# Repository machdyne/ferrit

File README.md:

# FERRIT Digital Archival Platform

FERRIT is a century-scale digital archival platform based on Ferroelectric RAM.

This repo contains PCB layouts, schematics, firmware and documentation.

Find more information on the [FERRIT project page](https://machdyne.com/ferrit/).

## Hardware

FERRIT is a modular upgradable system with 3 component types:

- A controller
- A backplane
- Removable ferroelectric memory cards

The controller communicates with the memory cards over a SPI/QSPI bus and exposes the memory to an interface, such as a USB mass storage device.

### Specifications

- Max capacity: 256MB+
- Max addressable memory devices per memory card: 16
- Max addressable memory devices per system: 256
- Interface: Depends on controller
- Speed: Depend on controller

*Note: The max capacity assumes double-sided memory cards with 1MB ICs. Higher capacities may be possible in the future.*

### Components

| Board | Type | Notes |
| ----- | ---- | ----- |
| [FERRIT-CY](https://machdyne.com/product/ferrit-cy/) | Controller | RP2040 / USB-FS |
| [FERRIT-M8](https://machdyne.com/product/ferrit-m8-8mb/) | Memory card | 8 x SOP-16 |
| [FERRIT-1](https://machdyne.com/product/ferrit-1/) | Backplane + Controller | RP2040 / USB-FS / 1 memory card slot |
| [FERRIT-8](https://machdyne.com/product/ferrit-8/) | Backplane | 8 memory card slots (1U rack-mount) |
| [FERRIT-16](https://machdyne.com/product/ferrit-16/) | Backplane | 16 memory card slots |

## Firmware

The firmware can be updated by holding down the BOOT button while plugging in the USB cable, and then dragging and dropping a new UF2 file to the device.

You can build the firmware from source, if you have [pico-sdk](https://github.com/raspberrypi/pico-sdk) installed:

```
$ cd firmware/ferrit
$ mkdir build
$ cd build
$ cmake .. -DPICO_DEFAULT_BOOT_STAGE2_FILE=$PICO_SDK_PATH/src/rp2040/boot_stage2/boot2_generic_03h.S
$ make
```

## Pinouts

### Connector

The FERRIT controller and memory cards use the same form-factor and share certain signals:

| Pin | Controller | Memory Card |
| --- | ---------- | ----------- |
| 1 | QSPI\_SCLK | QSPI\_SCLK |
| 3 | GND | GND |
| 5 | QSPI\_SD0 | QSPI\_SD0 |
| 7 | GND | GND |
| 9 | QSPI\_SD1 | QSPI\_SD1 |
| 11 | GND | GND |
| 13 | QSPI\_SD2 | QSPI\_SD2 |
| 15 | GND | GND |
| 17 | QSPI\_SD3 | QSPI\_SD3 |
| 19 | GND | GND |
| 2 | QSPI\_SS | QSPI\_SS |
| 4 | SS0 | GND |
| 6 | CS0 | CS0 |
| 8 | CS1 | CS1 |
| 10 | CS2 | CS2 |
| 12 | CS3 | CS3 |
| 14 | SS1 | GND |
| 16 | SS2 | GND |
| 18 | SS3 | GND |
| 20 | PWR3V3 | PWR3V3 |

The slot select (SSx) signals determine which slot is selected, while the chip select (CSx) signals select an IC on that slot.

## License

The contents of this repo are released under the [Lone Dynamics Open License](LICENSE.md).

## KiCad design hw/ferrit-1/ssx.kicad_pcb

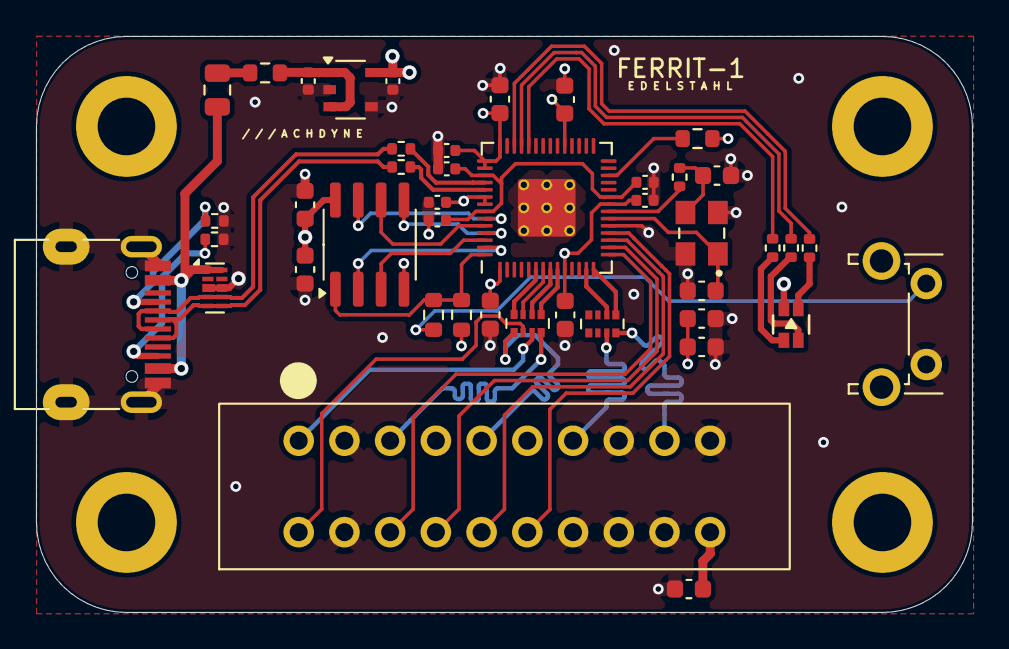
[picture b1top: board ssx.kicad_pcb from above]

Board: 4 copper layers, 52.0 x 32.0 mm, 47 parts (0 on the bottom side), 45 nets.

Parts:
C1, C2: 15pF; C_0603_1608Metric
C3, C10, C16, C17: 1uF; C_0402_1005Metric
C4, C6, C8, C9: 100nF; C_0402_1005Metric
C5, C7, C11, C12, C13, C15: 100nF; C_0603_1608Metric
C14: 1uF; C_0603_1608Metric
C19, C20: 22uF; C_0603_1608Metric
D1: LED_RGB_ANODE; LED_RGB_0606_CHANZON
F1: Fuse_Small; Fuse_0805_2012Metric
FB1: Ferrite_Bead_Small; R_0603_1608Metric
H1, H2, H3, H4: MountingHole; MountingHole_3.2mm_M3_DIN965_Pad
J1: USB_C_Receptacle_USB2.0_16P; USB_C_Receptacle_HRO_TYPE-C-31-M-12-BIG-PADS-PASTE
J2: Conn_02x10_Odd_Even; MACHDYNE_EDGE_SOCKET_20P
R1, R7: 10K; R_0603_1608Metric
R2, R3: 27R; R_0402_1005Metric
R4, R11, R12, R13: 1K; R_0402_1005Metric
R5, R6: 5K1; R_0402_1005Metric
R8: 1K; R_0603_1608Metric
RN1, RN2: 33R; R_Array_Convex_4x0402
SW1: BOOT; SW_Tactile_SPST_Angled_PTS645Vx39-2LFS
U1: RP2040; RP2040-QFN-56-OFFICIAL
U2: TPD4E05U06DQAR; Diodes_UDFN-10_1.0x2.5mm_P0.5mm
U3: M95P32-IXMNT/E; SOIC-8_3.9x4.9mm_P1.27mm
U4: NCP115; TSOP-5_1.65x3.05mm_P0.95mm
Y1: ECS-80-12-33-JGN-TR-12MHZ; XTAL_ECS-240-8-33-AGN-TR

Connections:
/BOOT: R8.1, SW1.1
/CS0: J2.6, U1.15 (GPIO12)
/CS1: J2.8, U1.16 (GPIO13)
/CS2: J2.10, U1.17 (GPIO14)
/CS3: J2.12, U1.18 (GPIO15)
/KQSPI_SCLK: J2.1, RN1.7 (R2.2)
/KQSPI_SD0: J2.5, RN1.8 (R1.2)
/KQSPI_SD1: J2.9, RN1.5 (R4.2)
/KQSPI_SD2: J2.13, RN2.7 (R2.2)
/KQSPI_SD3: J2.17, RN2.8 (R1.2)
/KSS: J2.2, RN1.6 (R3.2)
/LEDB: R13.2, U1.40 (GPIO28/ADC2)
/LEDG: R12.2, U1.39 (GPIO27/ADC1)
/LEDR: R11.2, U1.38 (GPIO26/ADC0)
/PWR1V1: C6.1, C8.1, C10.1, U1.23 (DVDD), U1.45 (VREG_VOUT), U1.50 (DVDD)
/PWR3V3: C3.1, C4.1, C5.1, C7.1, C9.1, C11.1, C12.1, C13.1, C14.1, C15.1, C17.1, C19.1, C20.1, D1.1 (A), J2.20, R1.1, R7.1, U1.1 (IOVDD), U1.10 (IOVDD), U1.22 (IOVDD), U1.33 (IOVDD), U1.42 (IOVDD), U1.43 (ADC_AVDD), U1.44 (VREG_VIN), U1.48 (USB_VDD), U1.49 (IOVDD), U3.8 (VCC), U4.5 (OUT)
/PWR5V0: C16.1, FB1.1, U4.1 (IN), U4.3 (EN)
/QSPI_IO0: RN1.1 (R1.1), U1.9 (GPIO7)
/QSPI_IO1: RN1.4 (R4.1), U1.6 (GPIO4)
/QSPI_IO2: RN2.2 (R2.1), U1.13 (GPIO10)
/QSPI_IO3: RN2.1 (R1.1), U1.14 (GPIO11)
/QSPI_SCLK: RN1.2 (R2.1), U1.8 (GPIO6)
/RP_QSPI_IO0: U1.53 (QSPI_SD0), U3.5 (DI(IO0))
/RP_QSPI_IO1: U1.55 (QSPI_SD1), U3.2 (DO(IO1))
/RP_QSPI_IO2: U1.54 (QSPI_SD2), U3.3 (IO2)
/RP_QSPI_IO3: U1.51 (QSPI_SD3), U3.7 (IO3)
/RP_QSPI_SCK: U1.52 (QSPI_SCLK), U3.6 (CLK)
/RP_QSPI_SS: R7.2, R8.2, U1.56 (QSPI_CSN), U3.1 (~CS)
/RUN: R1.2, U1.26 (RUN)
/SS: RN1.3 (R3.1), U1.7 (GPIO5)
/USBCDN: J1.A7 (D-), J1.B7 (D-), R3.1, U2.4, U2.7
/USBCDP: J1.A6 (D+), J1.B6 (D+), R2.1, U2.5, U2.6
/USBC_CC1: J1.A5 (CC1), R5.2
/USBC_CC2: J1.B5 (CC2), R6.2
/USBDN: R3.2, U1.46 (USB_DM)
/USBDP: R2.2, U1.47 (USB_DP)
/VBUS: F1.1, J1.A4 (VBUS), J1.A9 (VBUS), J1.B4 (VBUS), J1.B9 (VBUS), U2.1, U2.10
/XIN: C1.2, U1.20 (XIN), Y1.1 (IN/OUT)
/XOUT: R4.2, U1.21 (XOUT)
GND: C1.1, C2.2, C3.2, C4.2, C5.2, C6.2, C7.2, C8.2, C9.2, C10.2, C11.2, C12.2, C13.2, C14.2, C15.2, C16.2, C17.2, C19.2, C20.2, J1.A1 (GND), J1.A12 (GND), J1.B1 (GND), J1.B12 (GND), J1.S1 (SHIELD), J2.3, J2.4, J2.7, J2.11, J2.14, J2.15, J2.16, J2.18, J2.19, R5.1, R6.1, SW1.2, U1.19 (TESTEN), U1.57 (GND), U2.3 (VSS), U2.8 (VSS), U3.4 (GND), U4.2 (GND), U4.4 (GND2), Y1.2 (GND), Y1.4 (GND)
unnamed: D1.2 (BK), R13.1
unnamed: D1.4 (GK), R12.1
unnamed: D1.3 (RK), R11.1
unnamed: F1.2, FB1.2
unnamed: C2.1, R4.1, Y1.3 (OUT/IN)

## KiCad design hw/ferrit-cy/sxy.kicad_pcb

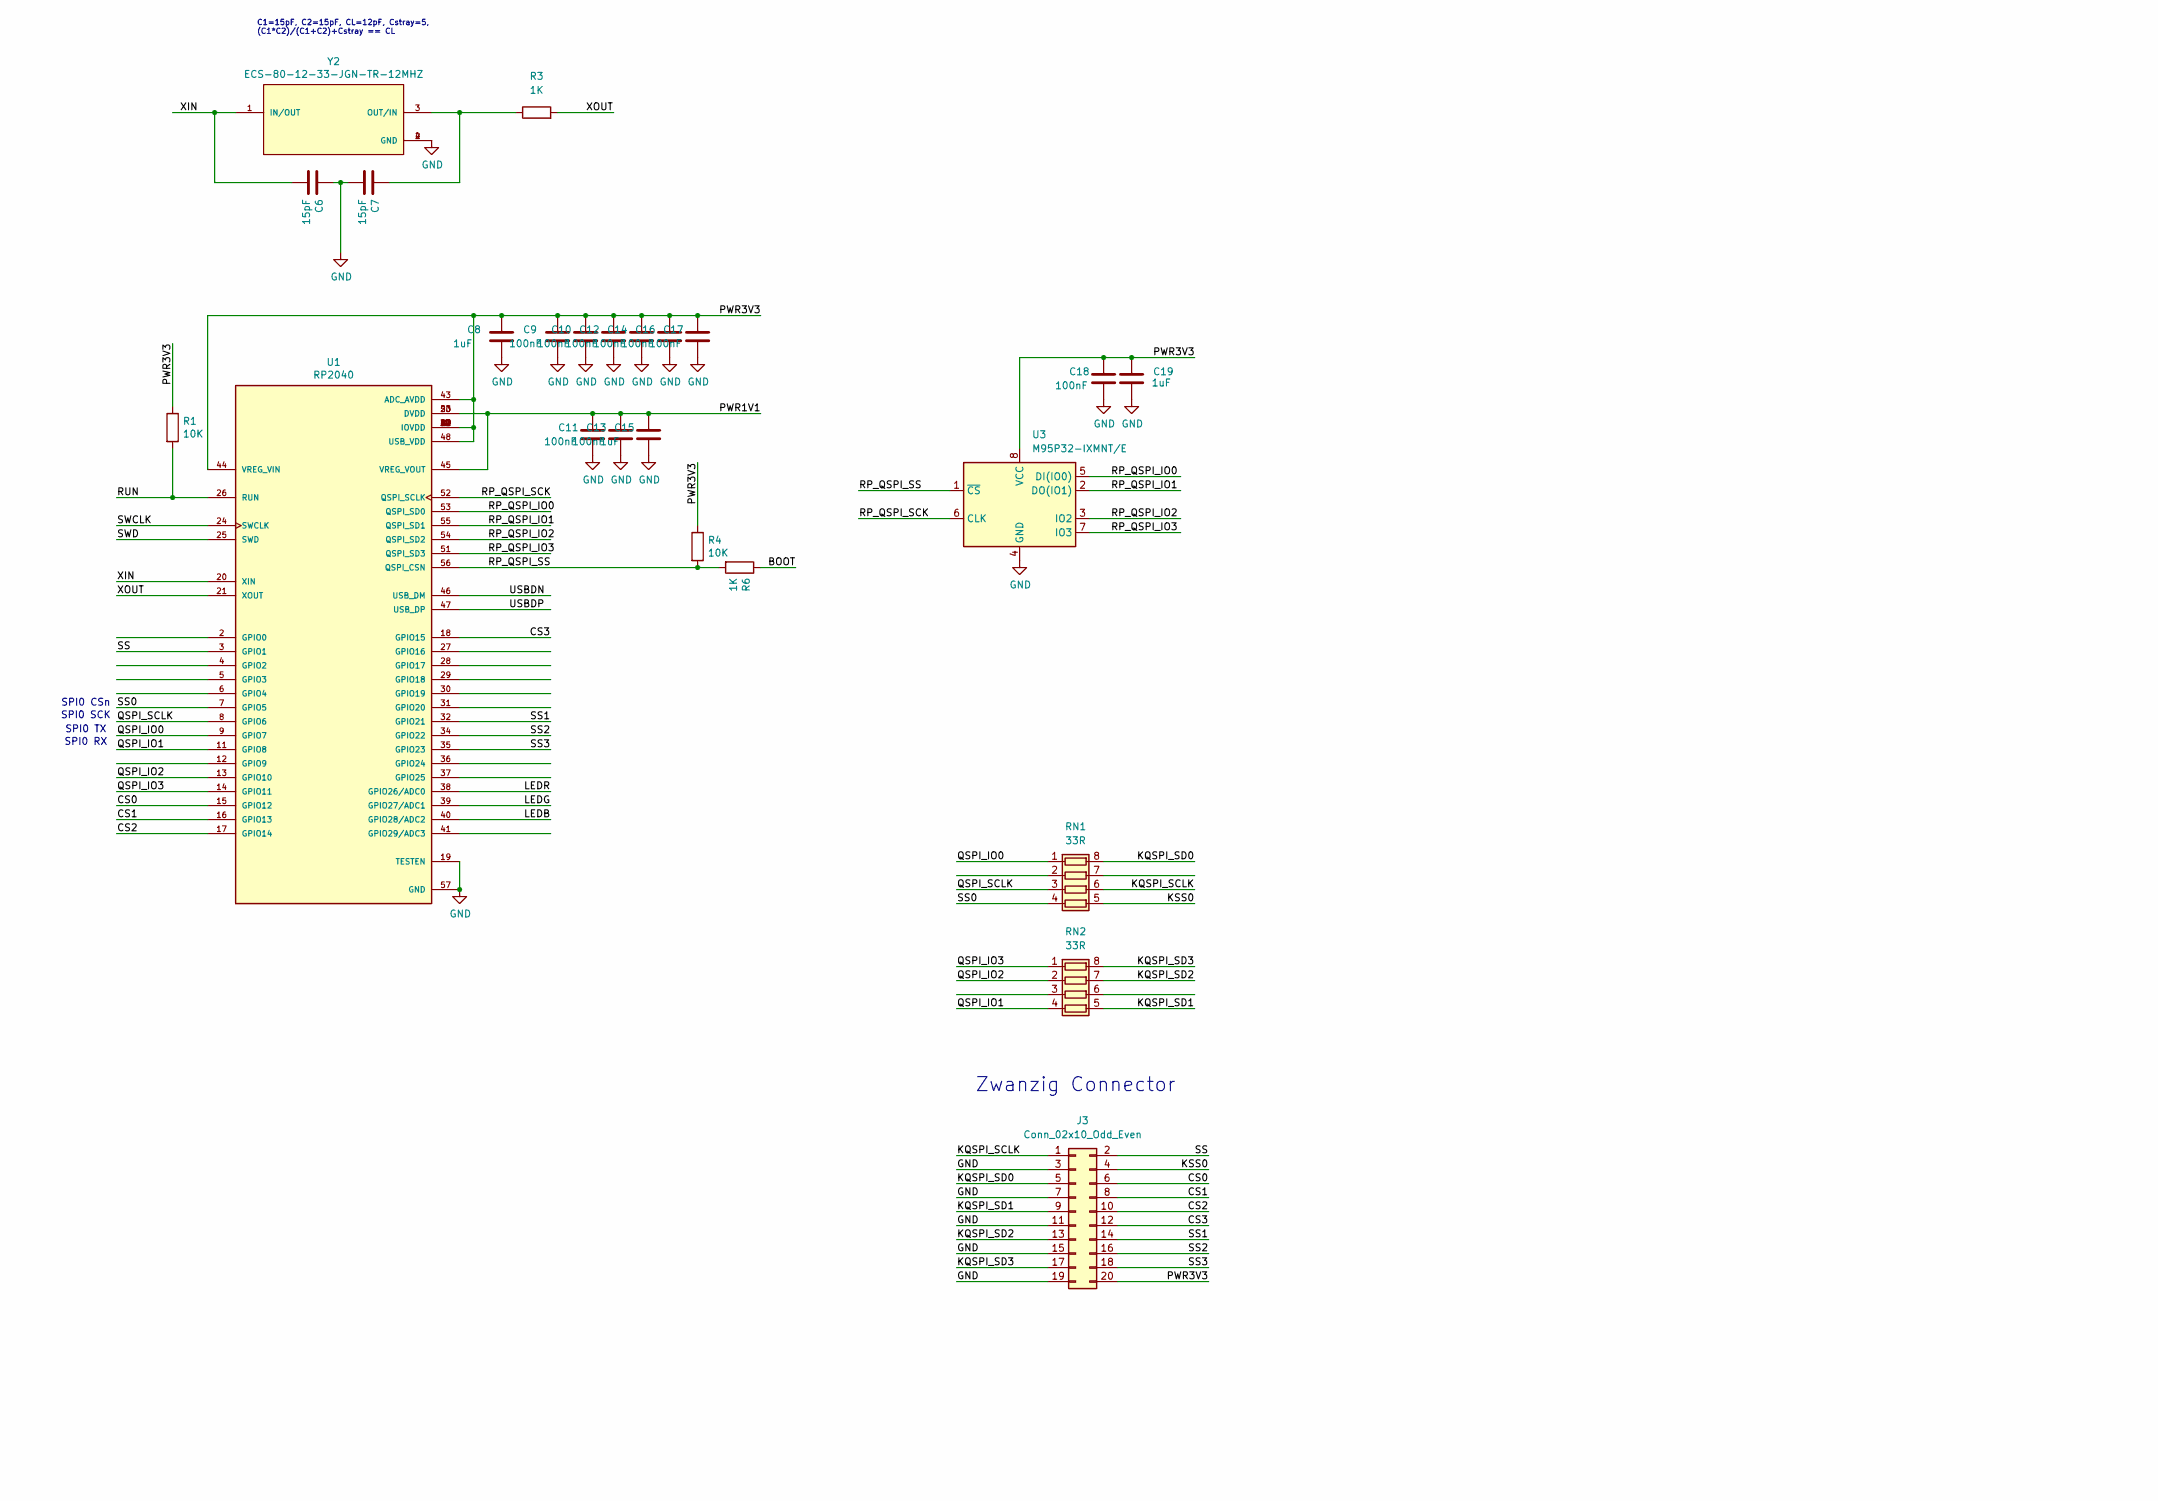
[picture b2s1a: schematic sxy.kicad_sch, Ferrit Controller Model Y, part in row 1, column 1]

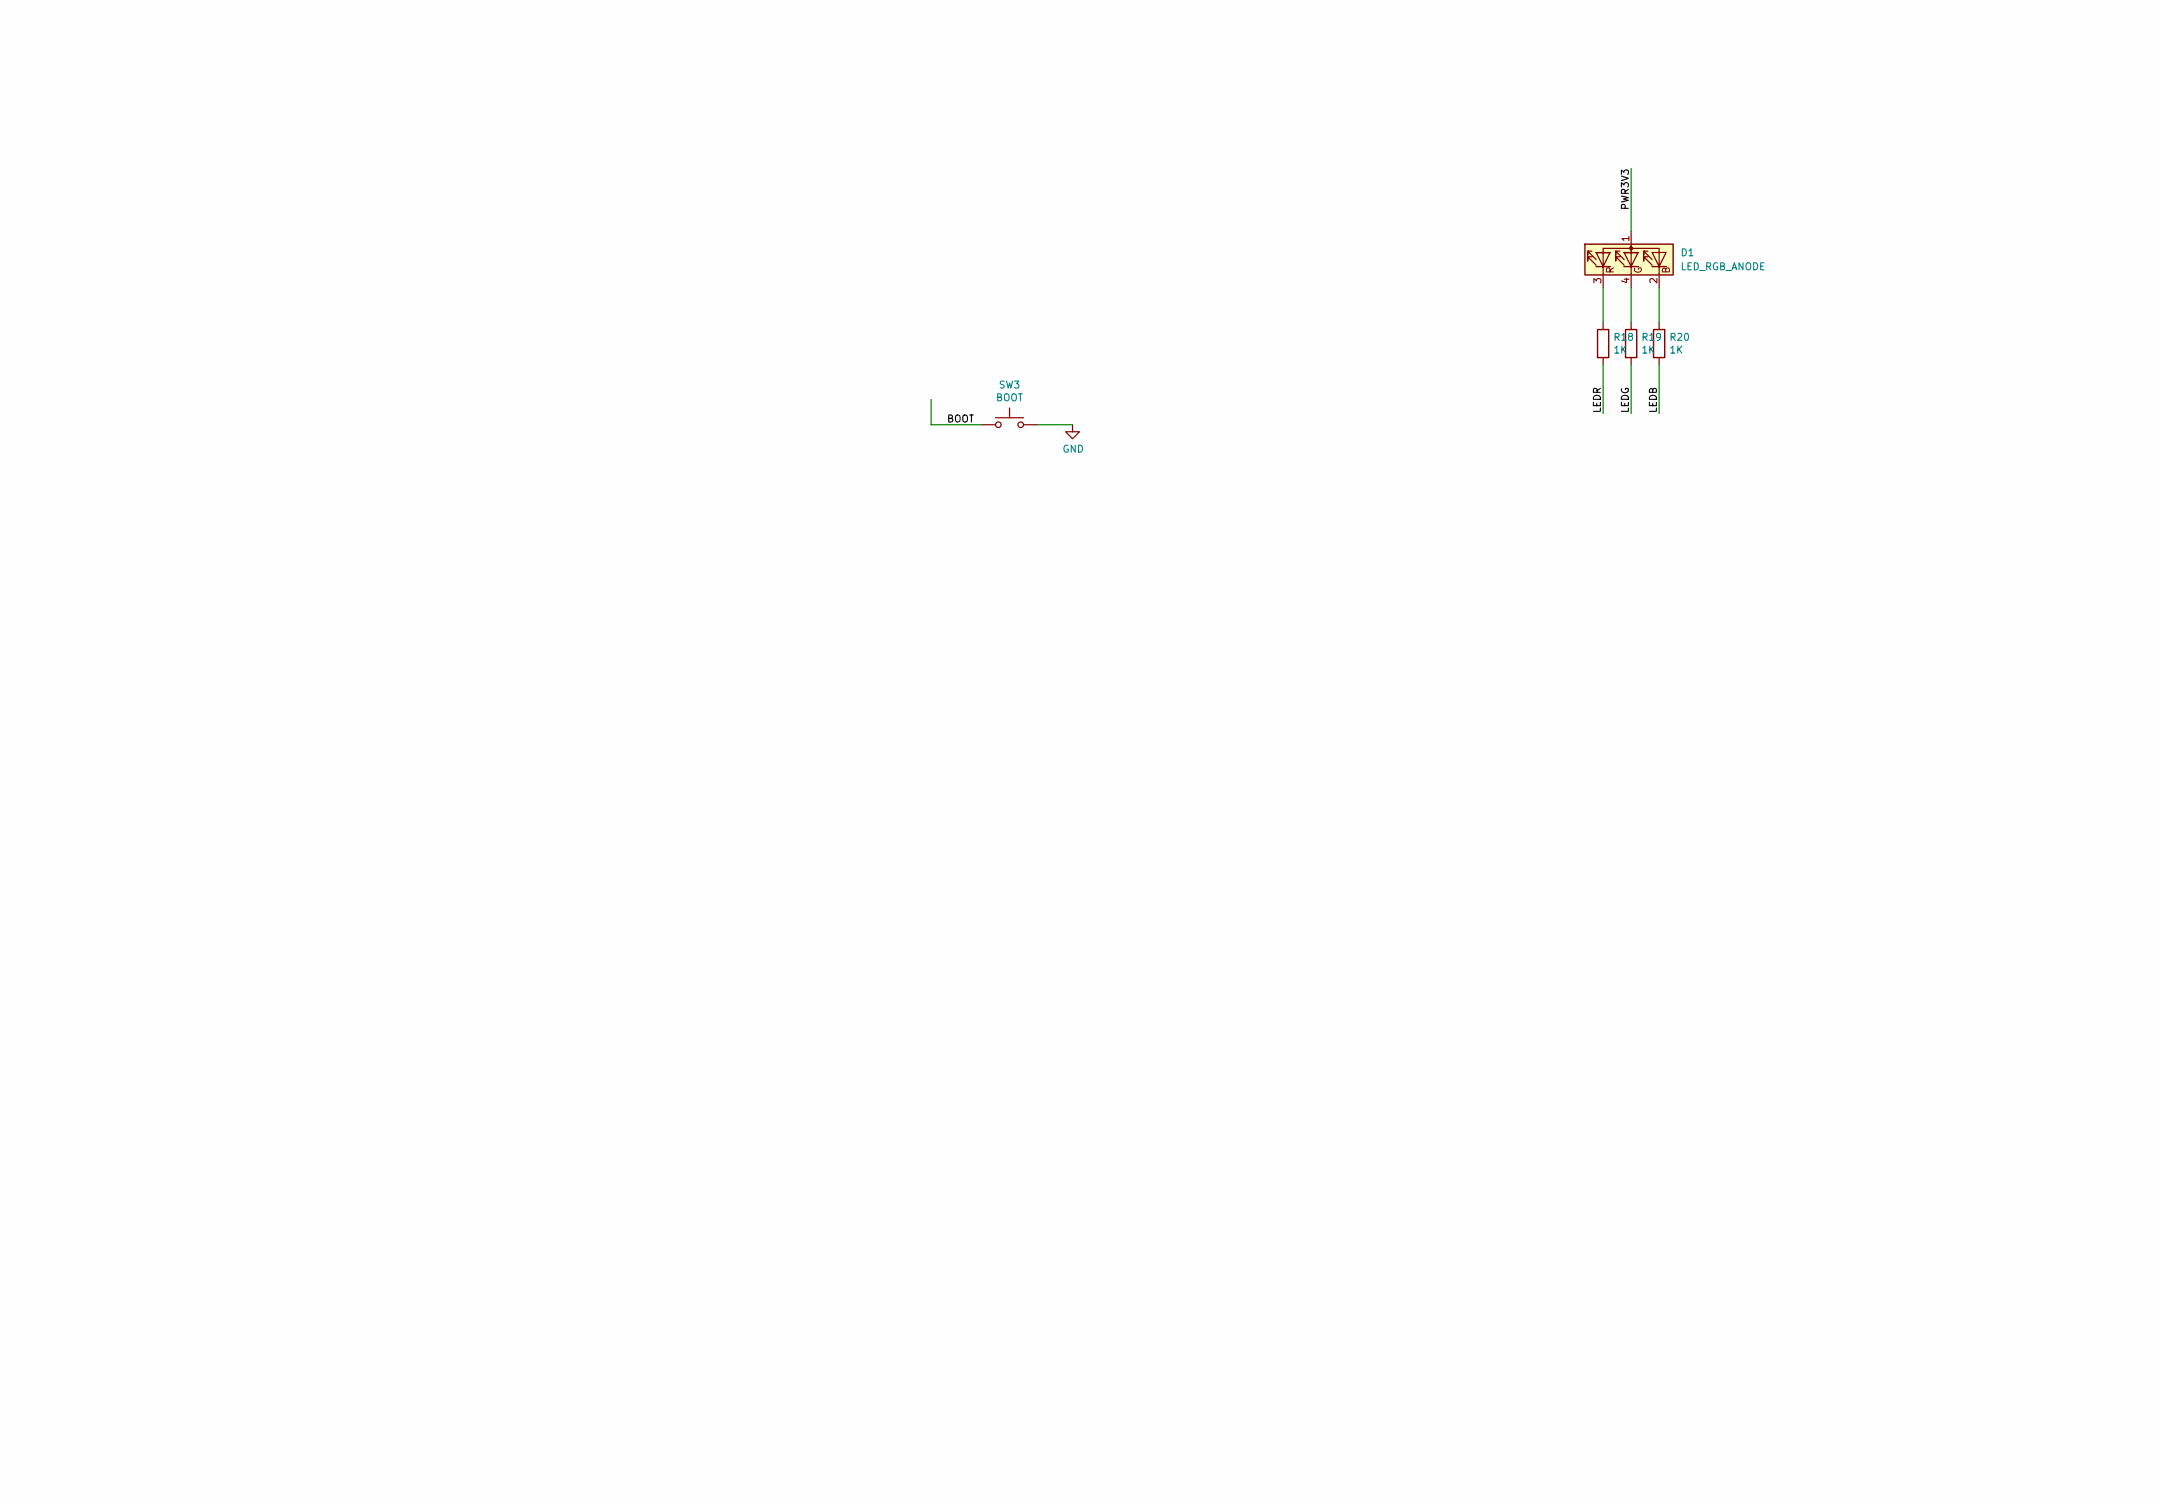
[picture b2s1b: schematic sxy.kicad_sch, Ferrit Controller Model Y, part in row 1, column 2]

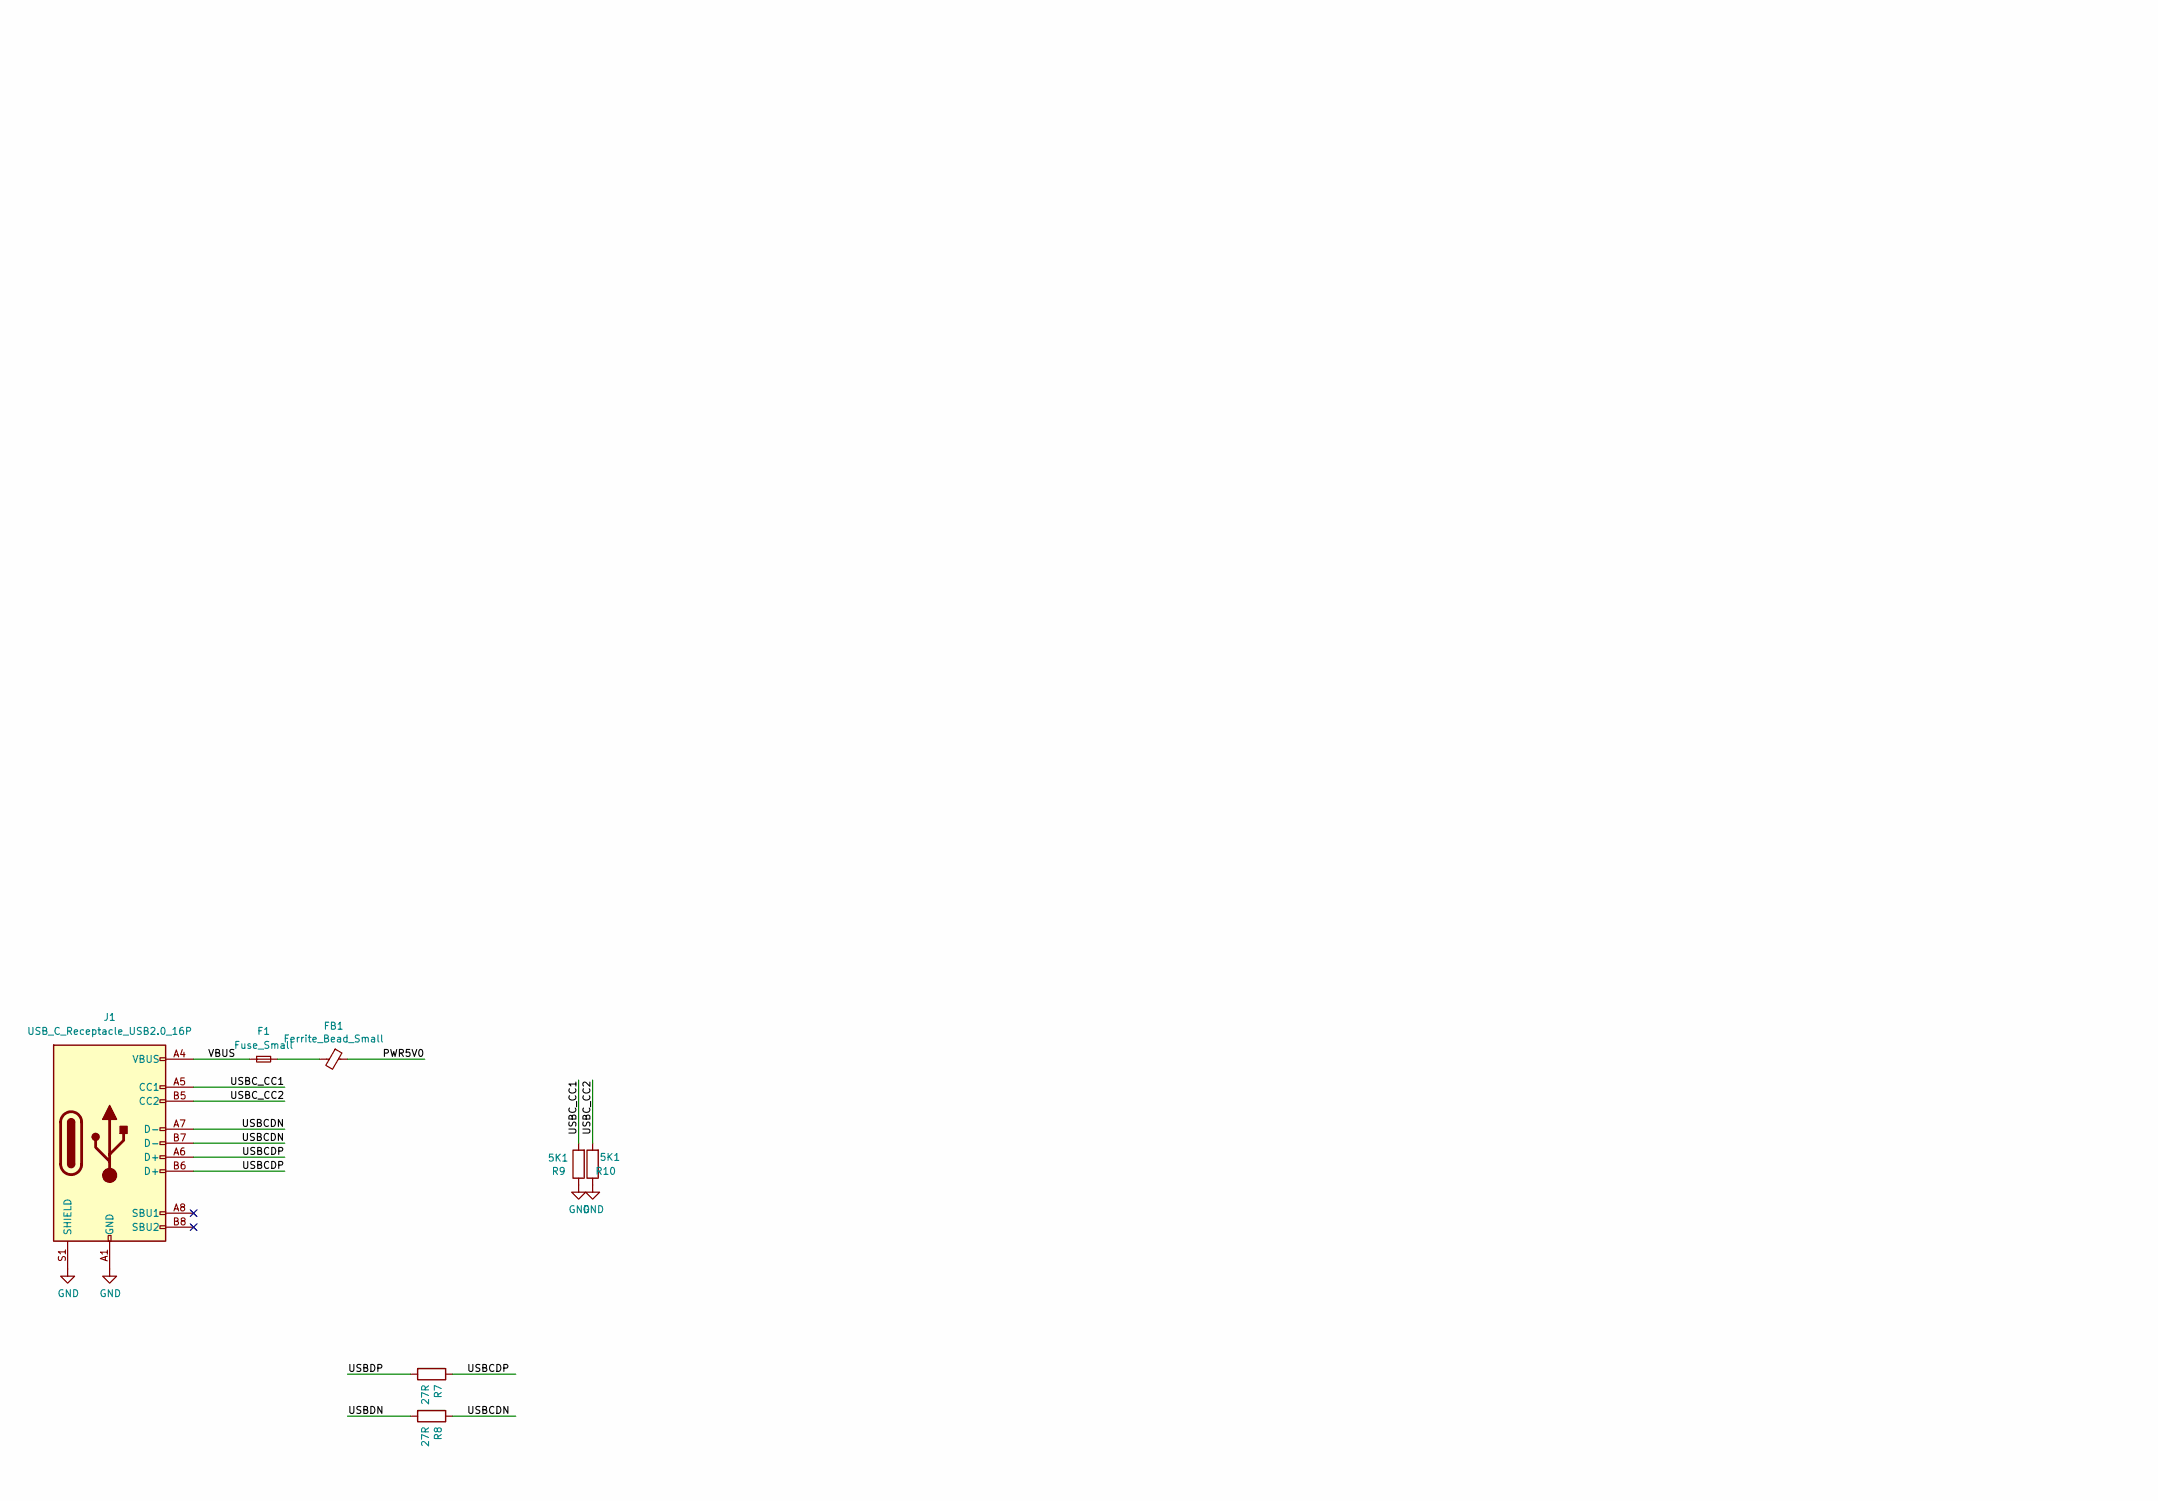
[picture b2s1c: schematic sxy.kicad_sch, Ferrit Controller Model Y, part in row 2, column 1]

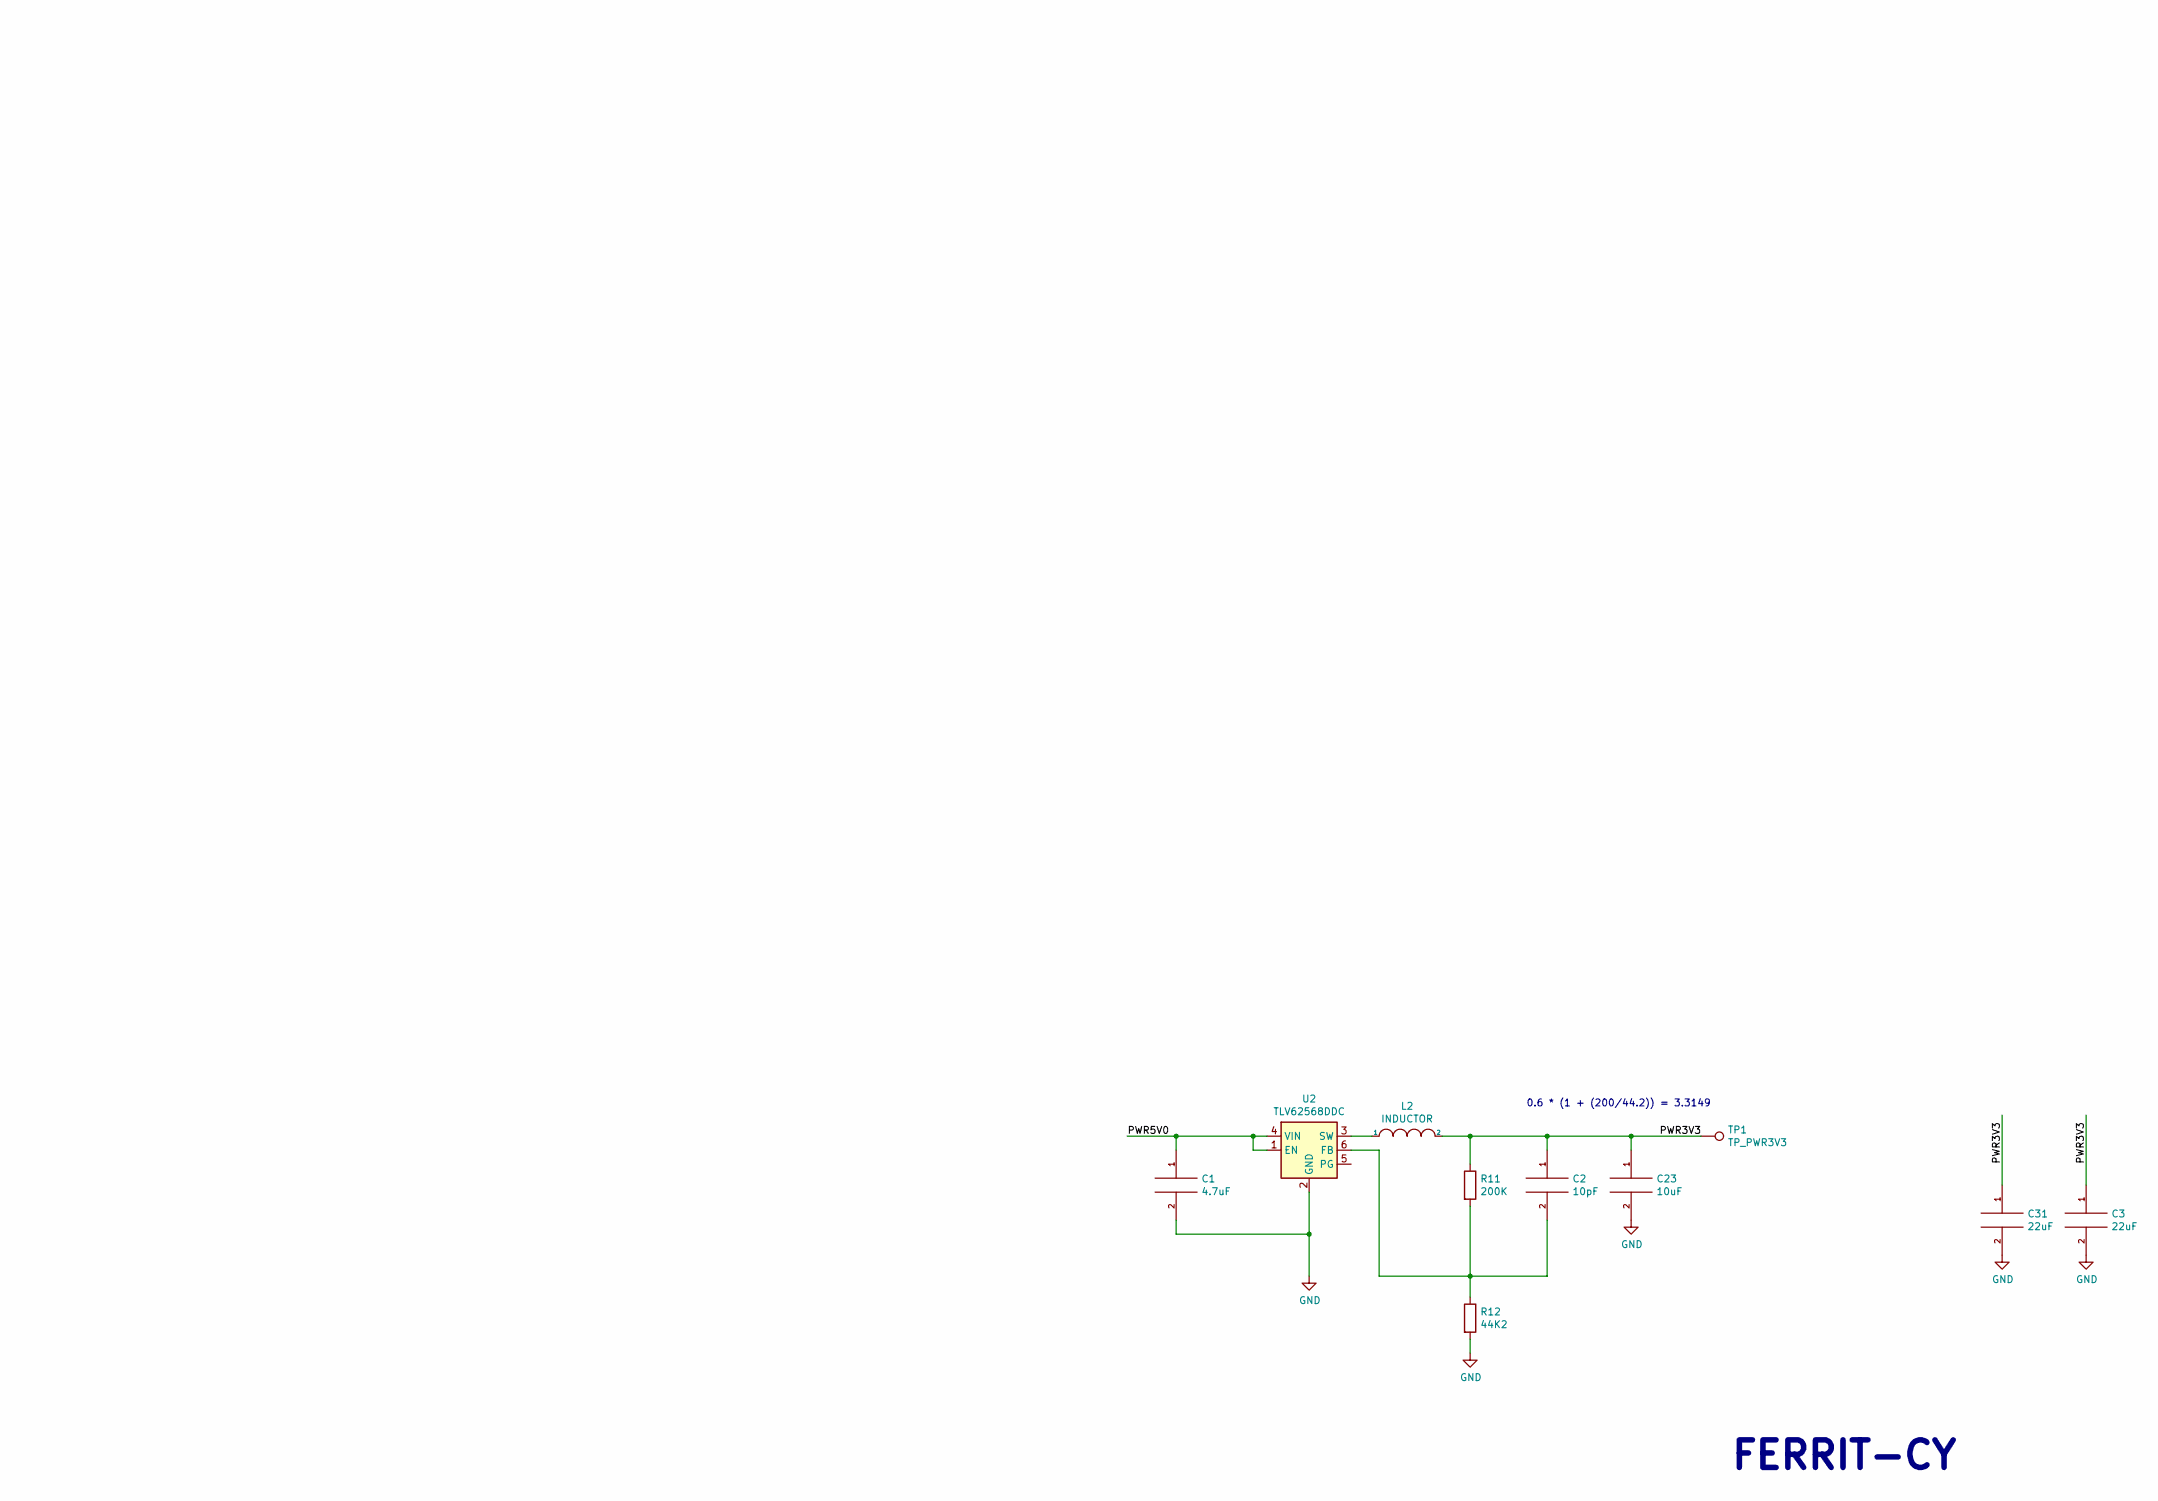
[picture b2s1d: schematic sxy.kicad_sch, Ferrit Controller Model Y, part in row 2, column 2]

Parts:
C1: 4.7uF; C_0603_1608Metric
C2: 10pF; C_0603_1608Metric
C3, C31: 22uF; C_0603_1608Metric
C6, C7: 15pF; C_0603_1608Metric
C8, C15: 1uF; C_0402_1005Metric
C9, C11, C13, C14: 100nF; C_0402_1005Metric
C10, C12, C16, C17, C18: 100nF; C_0603_1608Metric
C19: 1uF; C_0603_1608Metric
C23: 10uF; C_0603_1608Metric
D1: LED_RGB_ANODE; LED_RGB_0606_CHANZON
F1: Fuse_Small; Fuse_0805_2012Metric
FB1: Ferrite_Bead_Small; R_0603_1608Metric
J1: USB_C_Receptacle_USB2.0_16P; USB_C_Receptacle_HRO_TYPE-C-31-M-12-BIG-PADS-PASTE
J3: Conn_02x10_Odd_Even; MACHDYNE_EDGE_20P
L2: INDUCTOR; L_0805_2012Metric
R1, R4: 10K; R_0603_1608Metric
R3, R18, R19, R20: 1K; R_0402_1005Metric
R6: 1K; R_0603_1608Metric
R7, R8: 27R; R_0402_1005Metric
R9, R10: 5K1; R_0402_1005Metric
R11: 200K; R_0603_1608Metric
R12: 44K2; R_0603_1608Metric
RN1, RN2: 33R; R_Array_Convex_4x0402
SW3: BOOT; SW_SMD_2P_3X6MM
TP1: TP_PWR3V3; TestPoint_THTPad_D1.0mm_Drill0.5mm
U1: RP2040; RP2040-QFN-56-OFFICIAL; PARTREV 1.6.1
U2: TLV62568DDC; SOT-23-6
U3: M95P32-IXMNT/E; SOIC-8_3.9x4.9mm_P1.27mm
Y2: ECS-80-12-33-JGN-TR-12MHZ; XTAL_ECS-240-8-33-AGN-TR

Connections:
/BOOT: R6.1, SW3.1
/CS0: J3.6, U1.15 (GPIO12)
/CS1: J3.8, U1.16 (GPIO13)
/CS2: J3.10, U1.17 (GPIO14)
/CS3: J3.12, U1.18 (GPIO15)
/KQSPI_SCLK: J3.1, RN1.6 (R3.2)
/KQSPI_SD0: J3.5, RN1.8 (R1.2)
/KQSPI_SD1: J3.9, RN2.5 (R4.2)
/KQSPI_SD2: J3.13, RN2.7 (R2.2)
/KQSPI_SD3: J3.17, RN2.8 (R1.2)
/KSS0: J3.4, RN1.5 (R4.2)
/LEDB: R20.2, U1.40 (GPIO28/ADC2)
/LEDG: R19.2, U1.39 (GPIO27/ADC1)
/LEDR: R18.2, U1.38 (GPIO26/ADC0)
/PWR1V1: C11.1, C13.1, C15.1, U1.23 (DVDD), U1.45 (VREG_VOUT), U1.50 (DVDD)
/PWR3V3: C2.1, C3.1, C8.1, C9.1, C10.1, C12.1, C14.1, C16.1, C17.1, C18.1, C19.1, C23.1, C31.1, D1.1 (A), J3.20, L2.2, R1.1, R4.1, R11.1, TP1.1, U1.1 (IOVDD), U1.10 (IOVDD), U1.22 (IOVDD), U1.33 (IOVDD), U1.42 (IOVDD), U1.43 (ADC_AVDD), U1.44 (VREG_VIN), U1.48 (USB_VDD), U1.49 (IOVDD), U3.8 (VCC)
/PWR5V0: C1.1, FB1.1, U2.1 (EN), U2.4 (VIN)
/QSPI_IO0: RN1.1 (R1.1), U1.9 (GPIO7)
/QSPI_IO1: RN2.4 (R4.1), U1.11 (GPIO8)
/QSPI_IO2: RN2.2 (R2.1), U1.13 (GPIO10)
/QSPI_IO3: RN2.1 (R1.1), U1.14 (GPIO11)
/QSPI_SCLK: RN1.3 (R3.1), U1.8 (GPIO6)
/RP_QSPI_IO0: U1.53 (QSPI_SD0), U3.5 (DI(IO0))
/RP_QSPI_IO1: U1.55 (QSPI_SD1), U3.2 (DO(IO1))
/RP_QSPI_IO2: U1.54 (QSPI_SD2), U3.3 (IO2)
/RP_QSPI_IO3: U1.51 (QSPI_SD3), U3.7 (IO3)
/RP_QSPI_SCK: U1.52 (QSPI_SCLK), U3.6 (CLK)
/RP_QSPI_SS: R4.2, R6.2, U1.56 (QSPI_CSN), U3.1 (~CS)
/RUN: R1.2, U1.26 (RUN)
/SS: J3.2, U1.3 (GPIO1)
/SS0: RN1.4 (R4.1), U1.7 (GPIO5)
/SS1: J3.14, U1.32 (GPIO21)
/SS2: J3.16, U1.34 (GPIO22)
/SS3: J3.18, U1.35 (GPIO23)
/SWCLK: U1.24 (SWCLK)
/SWD: U1.25 (SWD)
/USBCDN: J1.A7 (D-), J1.B7 (D-), R8.1
/USBCDP: J1.A6 (D+), J1.B6 (D+), R7.1
/USBC_CC1: J1.A5 (CC1), R9.2
/USBC_CC2: J1.B5 (CC2), R10.2
/USBDN: R8.2, U1.46 (USB_DM)
/USBDP: R7.2, U1.47 (USB_DP)
/VBUS: F1.1, J1.A4 (VBUS), J1.A9 (VBUS), J1.B4 (VBUS), J1.B9 (VBUS)
/XIN: C6.2, U1.20 (XIN), Y2.1 (IN/OUT)
/XOUT: R3.2, U1.21 (XOUT)
GND: C1.2, C3.2, C6.1, C7.2, C8.2, C9.2, C10.2, C11.2, C12.2, C13.2, C14.2, C15.2, C16.2, C17.2, C18.2, C19.2, C23.2, C31.2, J1.A1 (GND), J1.A12 (GND), J1.B1 (GND), J1.B12 (GND), J1.S1 (SHIELD), J3.3, J3.7, J3.11, J3.15, J3.19, R9.1, R10.1, R12.2, SW3.2, U1.19 (TESTEN), U1.57 (GND), U2.2 (GND), U3.4 (GND), Y2.2 (GND), Y2.4 (GND)
unnamed: D1.2 (BK), R20.1
unnamed: D1.4 (GK), R19.1
unnamed: D1.3 (RK), R18.1
unnamed: F1.2, FB1.2
unnamed: C2.2, R11.2, R12.1, U2.6 (FB)
unnamed: L2.1, U2.3 (SW)
unnamed: C7.1, R3.1, Y2.3 (OUT/IN)

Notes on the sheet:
FERRIT-CY
0.6 * (1 + (200/44.2)) = 3.3149
SPI0 TX
C1=15pF, C2=15pF, CL=12pF, Cstray=5, (C1*C2)/(C1+C2)+Cstray == CL
Zwanzig Connector
SPI0 SCK
SPI0 CSn
SPI0 RX

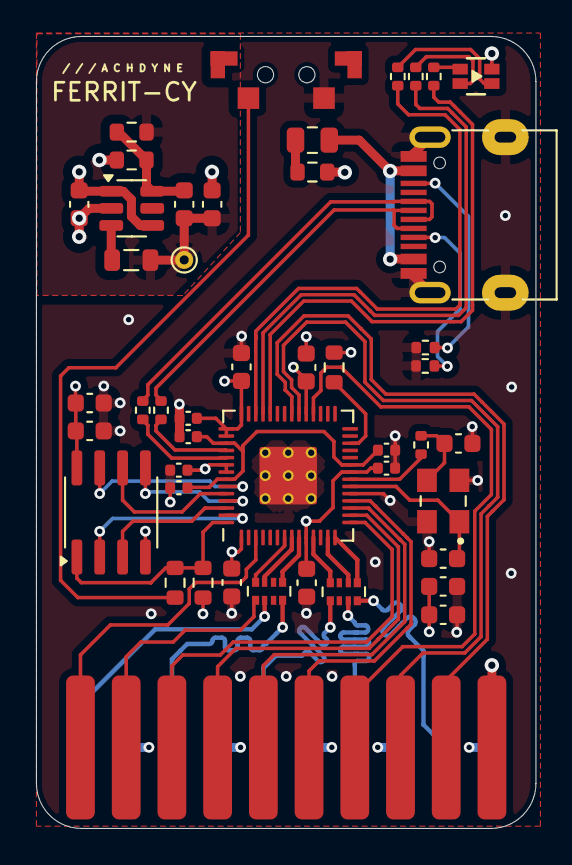
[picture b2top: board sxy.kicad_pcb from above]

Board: 4 copper layers, 27.8 x 44.0 mm, 46 parts (0 on the bottom side), 51 nets.

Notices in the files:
hw/ferrit-16/ssu.kicad_sch:
Copyright © 2026 Lone Dynamics Corporation
